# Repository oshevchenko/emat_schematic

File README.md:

# emat_schematic
Eagle schematic for 1000V power supply, HV switch, amplifier etc.

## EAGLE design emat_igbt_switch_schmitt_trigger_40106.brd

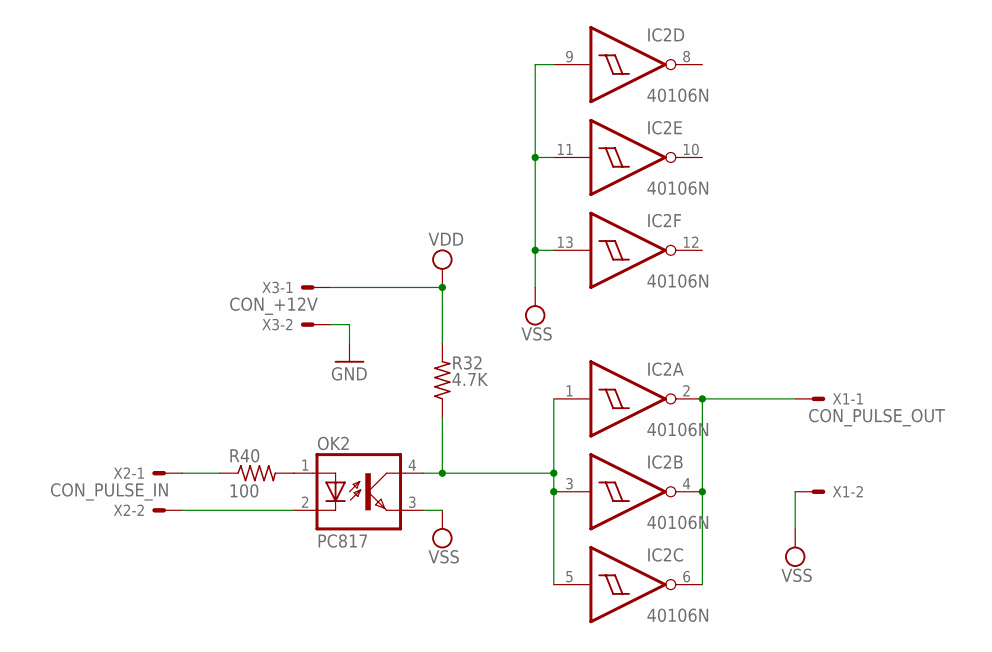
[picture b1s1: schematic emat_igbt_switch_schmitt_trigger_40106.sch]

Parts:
IC2: 40106N; DIL14
OK2: PC817; DIL04
R32: 4.7K; R1206
R40: 100; R1206
X1: CON_PULSE_OUT; 22-23-2021
X2: CON_PULSE_IN; 22-23-2021
X3: CON_+12V; 22-23-2021

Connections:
GND: X3.2
unnamed: IC2.2 (O), IC2.4 (O), IC2.6 (O), X1.1
unnamed: OK2.2 (C), X2.2
unnamed: IC2.1 (I), IC2.3 (I), IC2.5 (I), OK2.4 (COL), R32.1
unnamed: R40.1, X2.1
unnamed: OK2.1 (A), R40.2
VDD: IC2.14 (VDD), R32.2, X3.1
VSS: IC2.7 (VSS), IC2.9 (I), IC2.11 (I), IC2.13 (I), OK2.3 (EMIT), X1.2

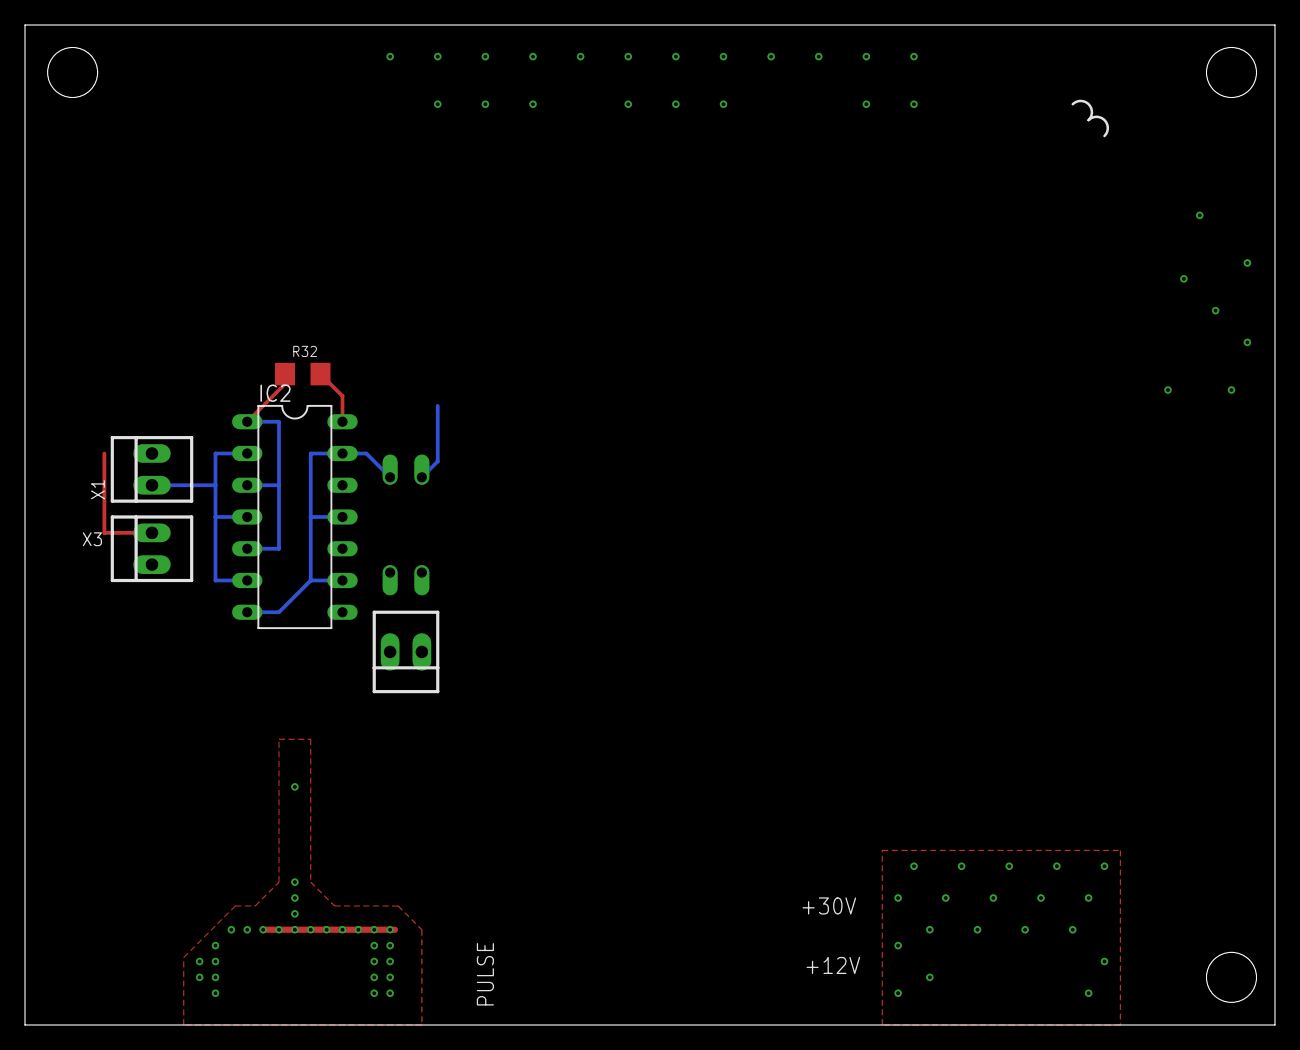
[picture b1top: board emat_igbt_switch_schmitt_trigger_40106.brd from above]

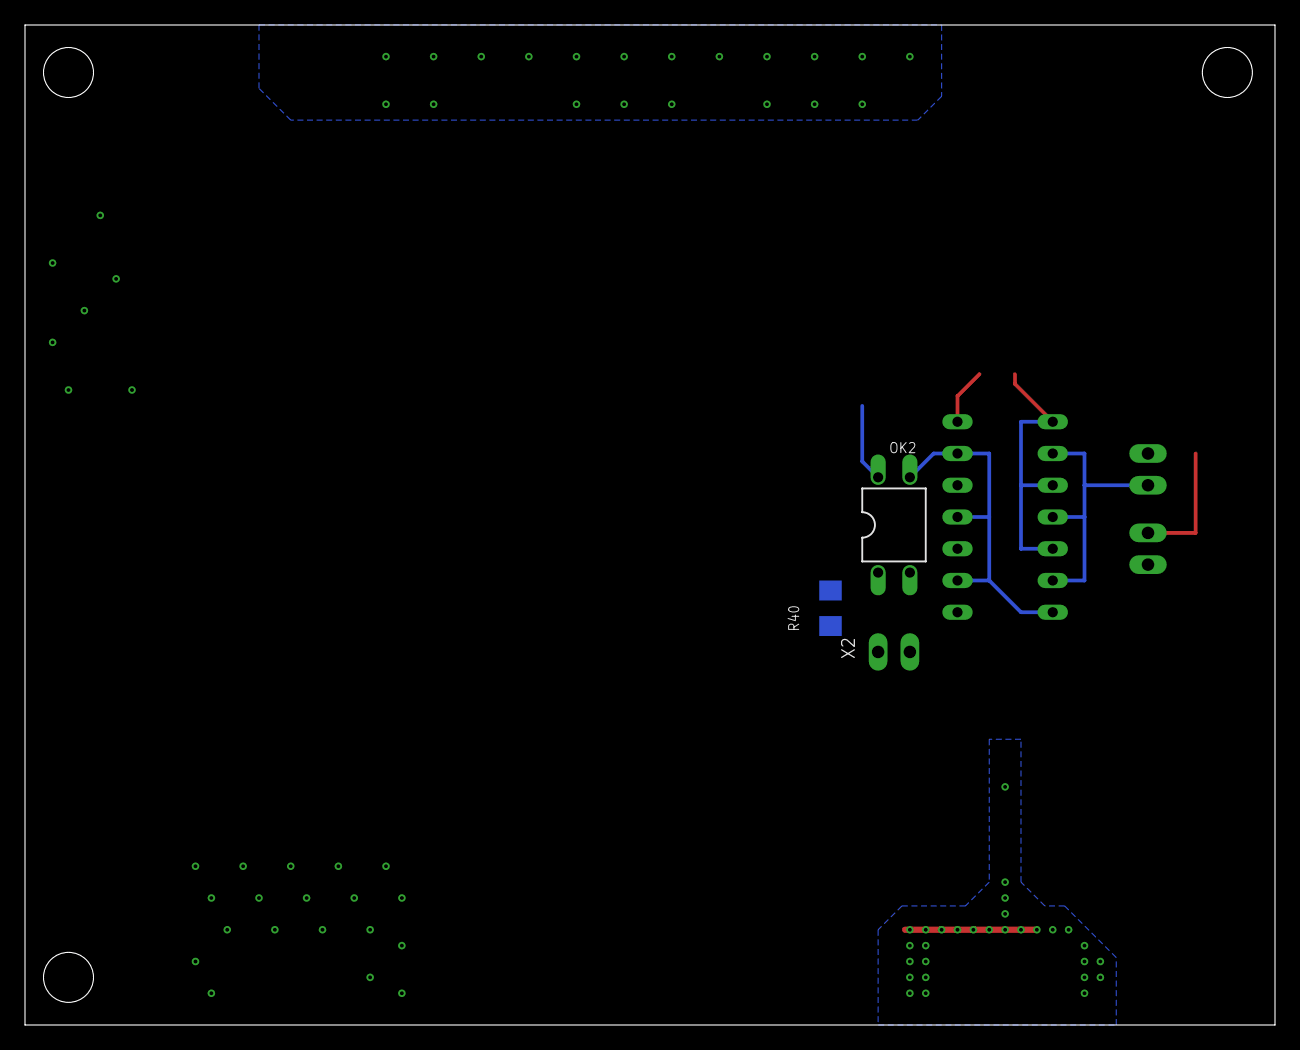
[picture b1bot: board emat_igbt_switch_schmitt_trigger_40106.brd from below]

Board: 2 copper layers, 100.0 x 80.0 mm, 7 parts (2 on the bottom side), 7 nets.

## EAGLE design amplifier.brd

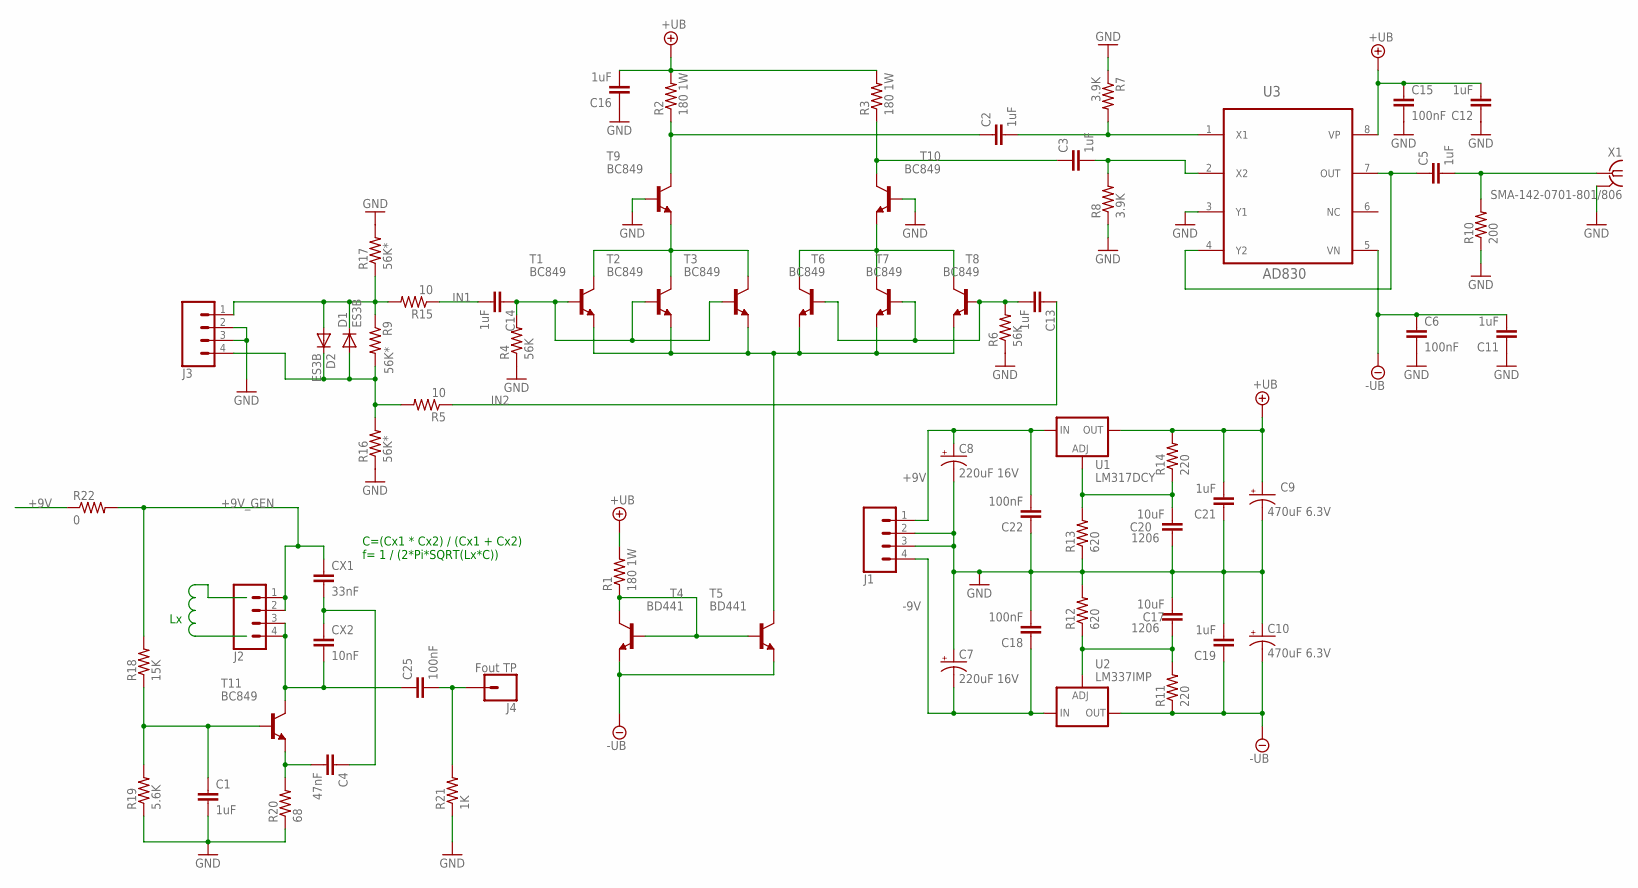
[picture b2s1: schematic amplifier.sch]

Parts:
C1, C2, C3, C5, C11, C12, C13, C14, C16, C19, C21: 1uF; C0805
C4: 47nF; C0805
C6, C15, C18, C22, C25: 100nF; C0805
C7, C8: 220uF 16V; 153CLV-1010
C9, C10: 470uF 6.3V; 153CLV-1010
C17, C20: 10uF; C1206
CX1: 33nF; C0805
CX2: 10nF; C0805
D1, D2: ES3B; SMC
J1, J2, J3: CONN_04LONGPADS; 1X04_LONGPADS
J4: Fout TP; SNAP-MALE
R1, R2, R3: 180 1W; R1206W
R4, R6: 56K; R1206W
R5, R15: 10; R1206W
R7, R8: 3.9K; R1206W
R9, R16, R17: 56K*; R1206W
R10: 200; R1206W
R11, R14: 220; R1206W
R12, R13: 620; R1206W
R18: 15K; R1206W
R19: 5.6K; R1206W
R20: 68; R1206W
R21: 1K; R1206W
R22: 0; R1206W
T1, T2, T3, T6, T7, T8, T9, T10, T11: BC849; SOT23
T4, T5: BD441; TO126
U1: LM317DCY; SOT223
U2: LM337IMP; SOT223
U3: AD830; SOIC127P600X175-8N
X1: SMA-142-0701-801/806; J502-ND-142-0701-801/806

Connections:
+9V: C8.+, C22.2, J1.1, R22.1, U1.3 (IN)
+9V_GEN: CX1.1, J2.1, J2.2, R18.2, R22.2
+UB: C9.+, C12.2, C15.1, C16.2, C21.2, R1.2, R2.2, R3.2, R14.2, U1.2 (OUT), U1.4 (OUT), U3.8 (VP)
-9V: C7.-, C18.1, J1.4, U2.2 (IN), U2.4 (IN)
-UB: C6.1, C10.-, C11.2, C19.1, R11.1, T4.1 (E), T5.1 (E), U2.3 (OUT), U3.5 (VN)
GND: C1.2, C6.2, C7.+, C8.-, C9.-, C10.+, C11.1, C12.1, C15.2, C16.1, C17.2, C18.2, C19.2, C20.1, C21.1, C22.1, J1.2, J1.3, J3.2, J3.3, R4.1, R6.1, R7.1, R8.1, R10.1, R12.2, R13.1, R16.1, R17.2, R19.1, R20.1, R21.1, T9.1 (B), T10.1 (B), U3.3 (Y1), X1.G@1 (2), X1.G@2 (2), X1.G@3 (2), X1.G@4 (2)
IN1: C14.2, R15.1
IN2: C13.1, R5.1
unnamed: D1.C, D2.A, J3.1, R9.1, R15.2, R17.1
unnamed: C17.1, R11.2, R12.1, U2.1 (ADJ)
unnamed: D1.A, D2.C, J3.4, R5.2, R9.2, R16.2
unnamed: R1.1, T4.2 (C), T4.3 (B), T5.3 (B)
unnamed: C25.1, CX2.2, J2.3, J2.4, T11.3 (C)
unnamed: C2.2, R7.2, U3.1 (X1)
unnamed: C25.2, J4.2, R21.2
unnamed: C20.2, R13.2, R14.1, U1.1 (ADJ)
unnamed: C4.1, CX1.2, CX2.1
unnamed: C4.2, R20.2, T11.2 (E)
unnamed: T1.2 (E), T2.2 (E), T3.2 (E), T5.2 (C), T6.2 (E), T7.2 (E), T8.2 (E)
unnamed: C1.1, R18.1, R19.2, T11.1 (B)
unnamed: C13.2, R6.2, T6.1 (B), T7.1 (B), T8.1 (B)
unnamed: C14.1, R4.2, T1.1 (B), T2.1 (B), T3.1 (B)
unnamed: T1.3 (C), T2.3 (C), T3.3 (C), T9.2 (E)
unnamed: T6.3 (C), T7.3 (C), T8.3 (C), T10.2 (E)
unnamed: C2.1, R2.1, T9.3 (C)
unnamed: C3.1, R3.1, T10.3 (C)
unnamed: C3.2, R8.2, U3.2 (X2)
unnamed: C5.1, U3.4 (Y2), U3.7 (OUT)
unnamed: C5.2, R10.2, X1.1
NC: U3.6 (NC)

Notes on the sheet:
C=(Cx1 * Cx2) / (Cx1 + Cx2) f= 1 / (2*Pi*SQRT(Lx*C))

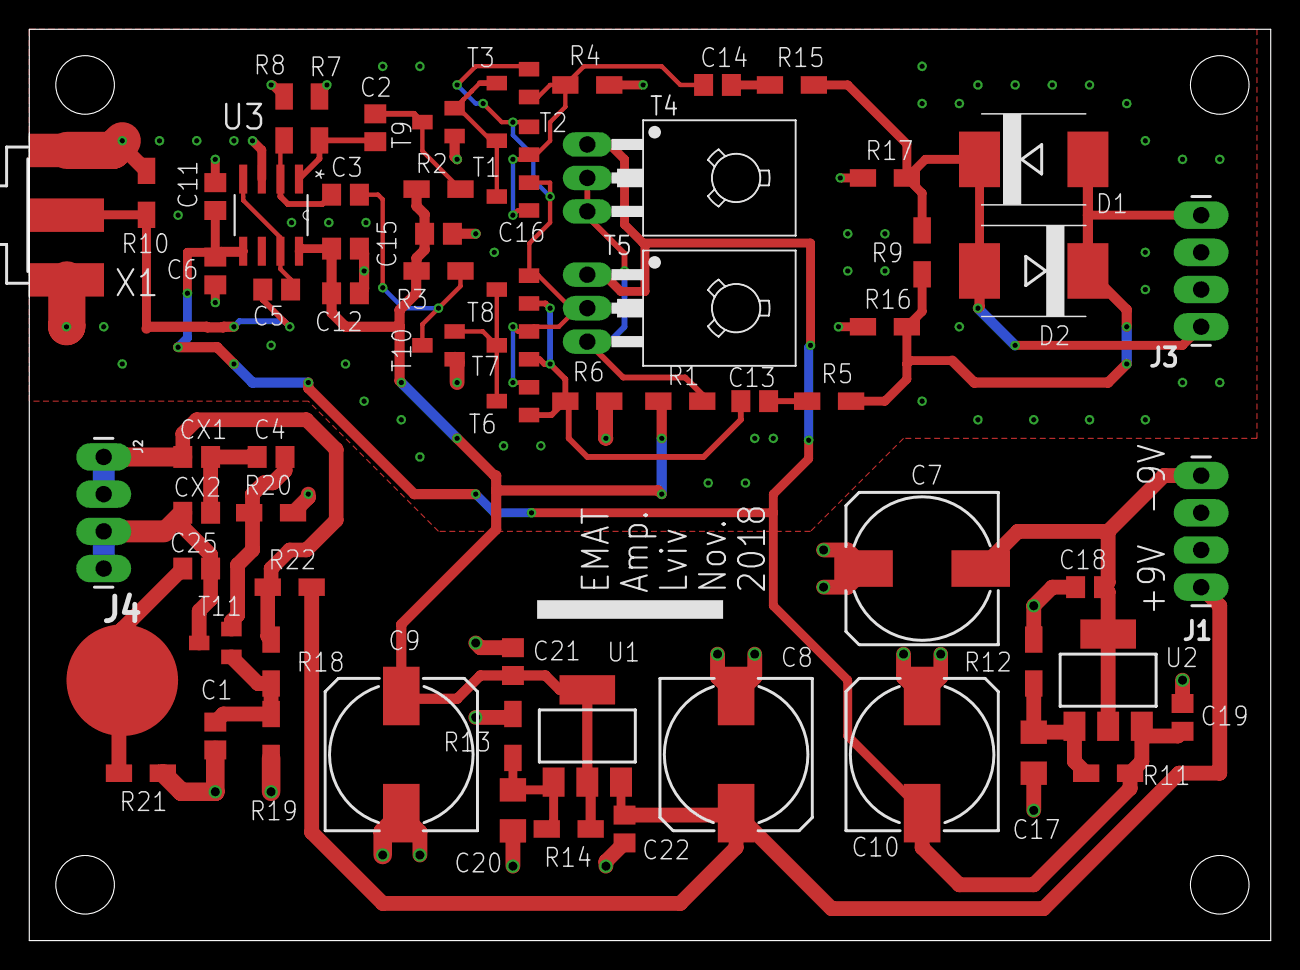
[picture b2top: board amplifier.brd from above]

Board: 2 copper layers, 84.8 x 62.2 mm, 68 parts (0 on the bottom side), 29 nets.

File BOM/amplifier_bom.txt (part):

Partlist exported from /home/oleksandr/EAGLE/projects/emat_schematic/amplifier.sch at 11/11/18 11:07 AM

Qty Value                Device               Package                  Parts                                             Description                                                                                                                              MF                 MPN          OC_FARNELL OC_NEWARK PACKAGE PROD_ID    SPICEPREFIX
3                        CONN_04LONGPADS      1X04_LONGPADS            J1, J2, J3                                        Multi connection point. Often used as Generic Header-pin footprint for 0.1 inch spaced/style header connections                                                                                       CONN-09696            
1   0                    R-US_R1206W          R1206W                   R22                                               RESISTOR, American symbol                                                                                                                                                                                                   
2   10                   R-US_R1206W          R1206W                   R5, R15                                           RESISTOR, American symbol                                                                                                                                                                                                   
5   100nF                C-EUC0805            C0805                    C6, C15, C18, C22, C25                            CAPACITOR, European symbol                                                                                                                                                                                                  
1   10nF                 C-EUC0805            C0805                    CX2                                               CAPACITOR, European symbol                                                                                                                                                                                                  
2   10uF                 C-EUC1206            C1206                    C17, C20                                          CAPACITOR, European symbol                                                                                                                                                                    1206                          
3   150 1W               R-US_R1206W          R1206W                   R1, R2, R3                                        RESISTOR, American symbol                                                                                                                                                                                                   
1   15K                  R-US_R1206W          R1206W                   R18                                               RESISTOR, American symbol                                                                                                                                                                                                   
1   1K                   R-US_R1206W          R1206W                   R21                                               RESISTOR, American symbol                                                                                                                                                                                                   
11  1uF                  C-EUC0805            C0805                    C1, C2, C3, C5, C11, C12, C13, C14, C16, C19, C21 CAPACITOR, European symbol                                                                                                                                                                                                  
1   200                  R-US_R1206W          R1206W                   R10                                               RESISTOR, American symbol                                                                                                                                                                                                   
2   220uF 16V            CPOL-US153CLV-1010   153CLV-1010              C7, C8                                            POLARIZED CAPACITOR, American symbol                                                                                                                                                                             C          
2   240                  R-US_R1206W          R1206W                   R11, R14                                          RESISTOR, American symbol                                                                                                                                                                                                   
2   3.9K                 R-US_R1206W          R1206W                   R7, R8                                            RESISTOR, American symbol                                                                                                                                                                                                   
1   33nF                 C-EUC0805            C0805                    CX1                                               CAPACITOR, European symbol                                                                                                                                                                                                  
2   470uF 6.3V           CPOL-US153CLV-1010   153CLV-1010              C9, C10                                           POLARIZED CAPACITOR, American symbol                                                                                                                                                                             C          
1   47nF                 C-EUC0805            C0805                    C4                                                CAPACITOR, European symbol                                                                                                                                                                                                  
1   5.6K                 R-US_R1206W          R1206W                   R19                                               RESISTOR, American symbol                                                                                                                                                                                                   
2   56K                  R-US_R1206W          R1206W                   R4, R6                                            RESISTOR, American symbol                                                                                                                                                                                                   
3   56K*                 R-US_R1206W          R1206W                   R9, R16, R17                                      RESISTOR, American symbol                                                                                                                                                                                                   
1   68                   R-US_R1206W          R1206W                   R20                                               RESISTOR, American symbol                                                                                                                                                                                                   
2   910                  R-US_R1206W          R1206W                   R12, R13                                          RESISTOR, American symbol                                                                                                                                                                                                   
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
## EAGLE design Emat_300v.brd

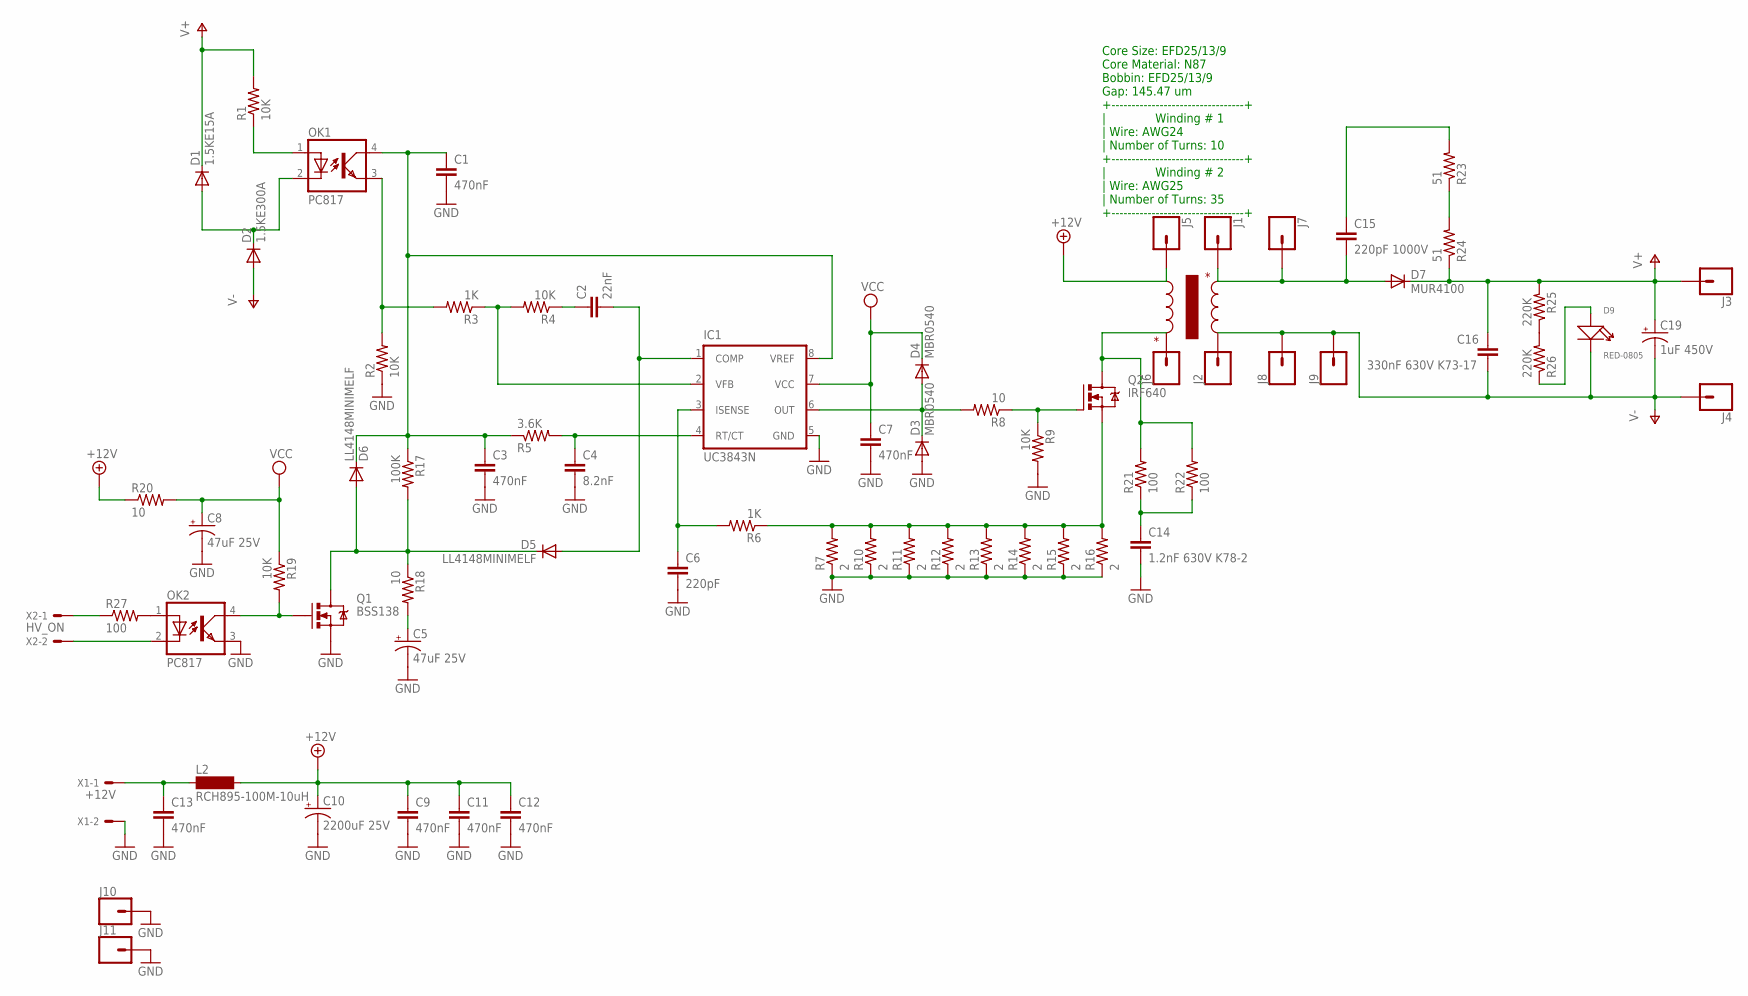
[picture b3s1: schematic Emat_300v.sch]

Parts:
C1, C3, C7, C9, C11, C12, C13: 470nF; C0805
C2: 22nF; C0805
C4: 8.2nF; C0805
C5, C8: 47uF 25V; E5-8,5
C6: 220pF; C0805
C10: 2200uF 25V; E7,5-18
C14: 1.2nF 630V K78-2; C150-064X183
C15: 220pF 1000V; C075-042X103
C16: 330nF 630V K73-17; C225-062X268
C19: 1uF 450V; E5-8,5
D1: 1.5KE15A; DO201-15
D2: 1.5KE300A; DO201-15
D3, D4: MBR0540; SOD123
D5, D6: LL4148MINIMELF; MINIMELF
D7: MUR4100; DO201-15
D9: RED-0805; LED-0805
IC1: UC3843N; DIL08
J1, J2, J3, J4, J5, J6, J7, J8, J9, J10, J11: CONN_01PTH_NO_SILK_KIT; 1X01NS_KIT
L2: RCH895-100M-10uH; BS11
OK1, OK2: PC817; DIL04
Q1: BSS138; SOT23-3
Q2: IRF640; TO220BV
R1, R2, R4, R9, R19: 10K; R1206
R3, R6: 1K; R1206
R5: 3.6K; R1206
R7, R10, R11, R12, R13, R14, R15, R16: 2; R1206
R8, R18, R20: 10; R1206
R17: 100K; R1206
R21, R22: 100; R2512
R23, R24: 51; R1206
R25, R26: 220K; R1206
R27: 100; R1206
X1: +12V; 22-23-2021
X2: HV_ON; 22-23-2021

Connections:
+12V: C9.1, C10.+, C11.1, C12.1, J5.1, L2.2, R20.1
GND: C1.2, C3.2, C4.2, C5.-, C6.2, C7.2, C8.-, C9.2, C10.-, C11.2, C12.2, C13.2, C14.2, D3.A, IC1.5 (GND), J10.1, J11.1, OK2.3 (EMIT), Q1.2 (S), R2.1, R7.1, R9.2, R10.1, R11.1, R12.1, R13.1, R14.1, R15.1, R16.1, X1.2
unnamed: D1.A, D2.C, OK1.2 (C)
unnamed: R25.1, R26.2
unnamed: OK1.1 (A), R1.1
unnamed: C5.+, R18.2
unnamed: OK1.3 (EMIT), R2.2, R3.2
unnamed: IC1.2 (VFB), R3.1, R4.2
unnamed: C2.1, R4.1
unnamed: C2.2, D5.A, IC1.1 (COMP)
unnamed: C4.1, IC1.4 (RT/CT), R5.2
unnamed: C6.1, IC1.3 (ISENSE), R6.2
unnamed: D3.C, D4.A, IC1.6 (OUT), R8.2
unnamed: Q2.G, R8.1, R9.1
unnamed: Q2.S, R6.1, R7.2, R10.2, R11.2, R12.2, R13.2, R14.2, R15.2, R16.2
unnamed: C1.1, C3.1, D6.C, IC1.8 (VREF), OK1.4 (COL), R5.1, R17.1
unnamed: D5.C, D6.A, Q1.3 (D), R17.2, R18.1
unnamed: C13.1, L2.1, X1.1
unnamed: OK2.4 (COL), Q1.1 (G), R19.2
unnamed: OK2.1 (A), R27.2
unnamed: OK2.2 (C), X2.2
unnamed: J6.1, Q2.D, R21.2, R22.2
unnamed: C14.1, R21.1, R22.1
unnamed: C15.2, D7.A, J1.1, J7.1
unnamed: R27.1, X2.1
unnamed: R23.1, R24.2
unnamed: C15.1, R23.2
unnamed: D9.+, R26.1
V+: C16.1, C19.+, D1.C, D7.C, J3.1, R1.2, R24.1, R25.2
V-: C16.2, C19.-, D2.A, D9.-, J2.1, J4.1, J8.1, J9.1
VCC: C7.1, C8.+, D4.C, IC1.7 (VCC), R19.1, R20.2

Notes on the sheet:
Core Size: EFD25/13/9 Core Material: N87 Bobbin: EFD25/13/9 Gap: 145.47 um +---------------------------------+ | Winding # 1 | Wire: AWG24 | Number of Turns: 10 +---------------------------------+ | Winding # 2 | Wire: AWG25 | Number of Turns: 35 +---------------------------------+

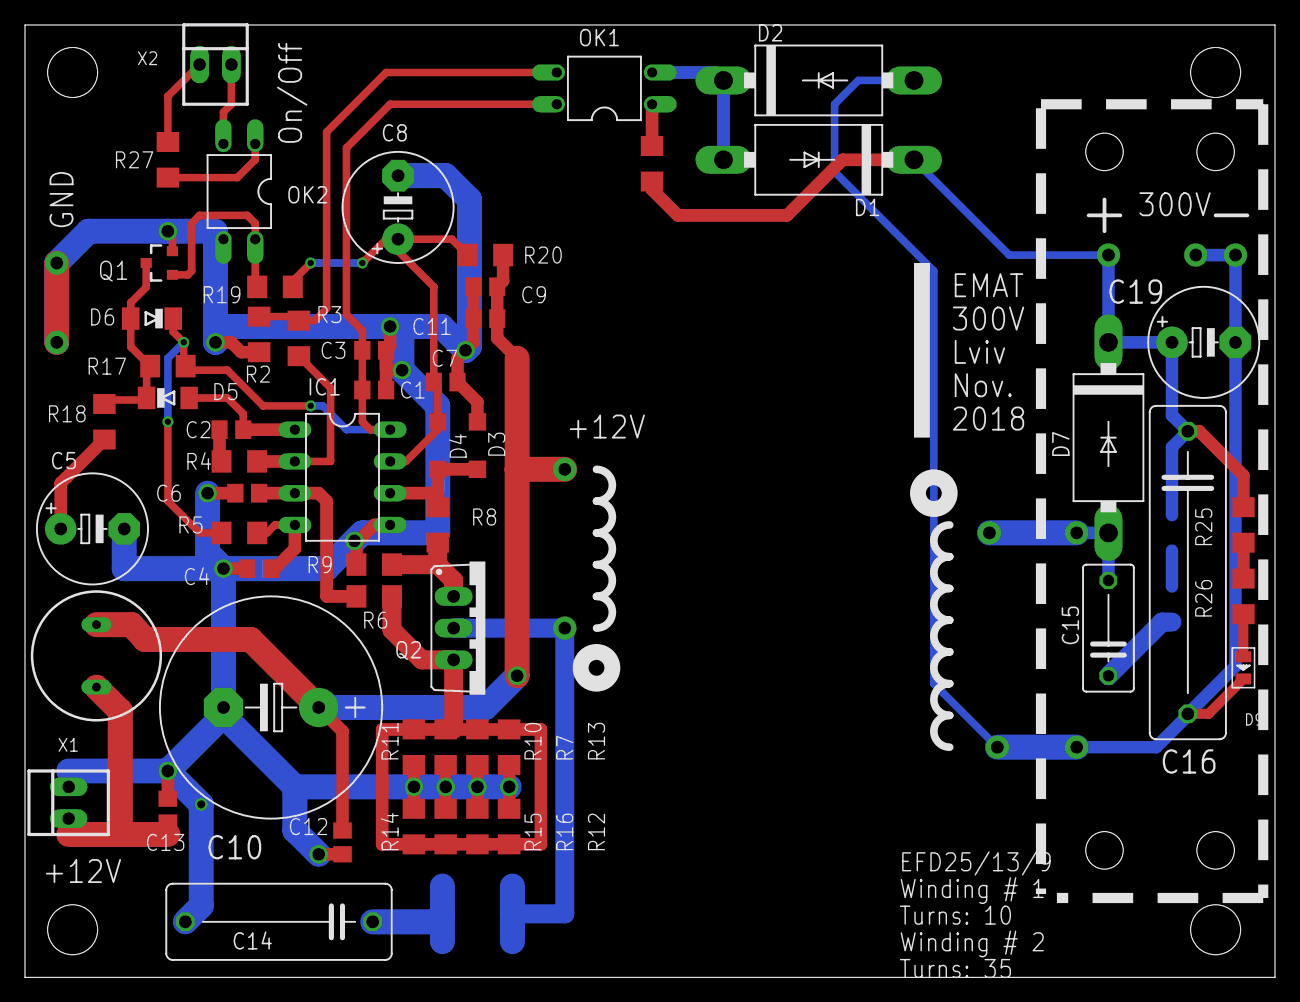
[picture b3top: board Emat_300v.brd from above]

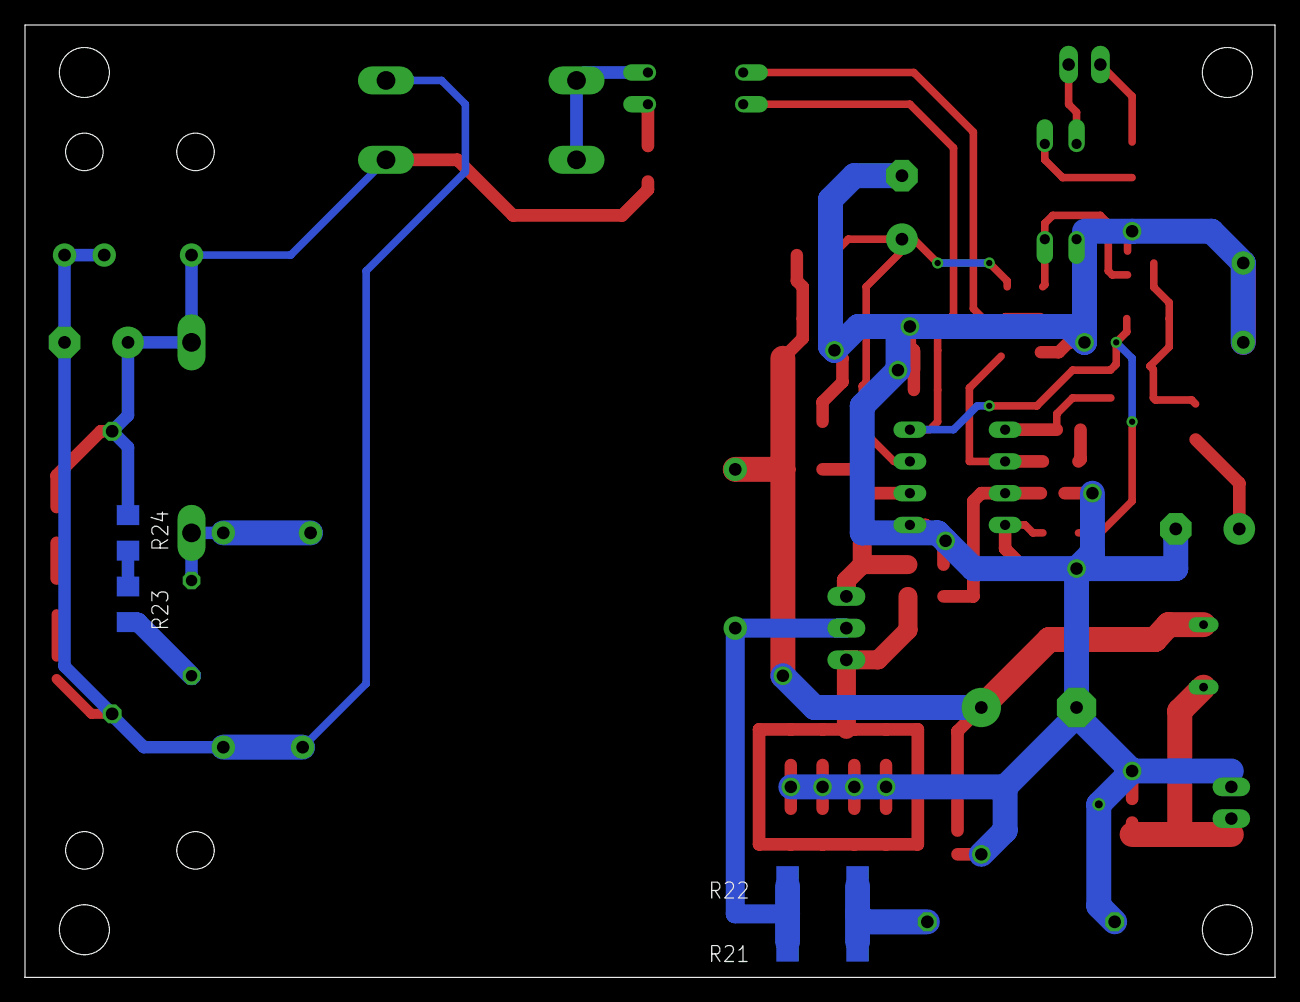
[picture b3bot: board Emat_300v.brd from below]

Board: 2 copper layers, 100.0 x 76.2 mm, 71 parts (4 on the bottom side), 31 nets.

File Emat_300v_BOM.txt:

Partlist exported from D:/workspace/EMAT/POC/Schematic/Emat/Emat_300v.sch at 4/7/2016 10:36 AM

Qty Value             Device                Package      Parts                                 Description
1   EFD25             EFD25                 EFD25        T1                                    TRANSFORMER
1   UC3843N           UC3843N               DIL08        IC1                                   SMPS Controller
1   BSS138            MOSFET-NCHANNELBSS138 SOT23-3      Q1                                    Common NMOSFET Parts
1   IRF640IW220B      IRF640IW220B          IW220B       Q2                                    HEXFET Power MOSFET
2   LL4148MINIMELF    LL4148MINIMELF        MINIMELF     D5, D6                                DIODE              
2   MBR0540           DIODE-SOD123          SOD123       D3, D4                                DIODE              
1   MUR4100           DIODE-DO201-15        DO201-15     D7                                    DIODE              
2   1.5KE15A          DIODE-DO201-15        DO201-15     D1, D2                                DIODE
2   PC817             PC817                 DIL04        OK1, OK2                              SHARP OPTO COUPLER
2   47uF 25V          CPOL-USE5-8.5         E5-8,5       C5, C8                                POLARIZED CAPACITOR
1   47uF 450V         CPOL-USE7.5-18        E7,5-18      C19                                   POLARIZED CAPACITOR
1   2200uF 25V        CPOL-USE7.5-18        E7,5-18      C10                                   POLARIZED CAPACITOR
1   1.2nF 630V K78-2  C-EU150-064X183       C150-064X183 C14                                   CAPACITOR
1   330nF 630V K73-17 C-EU225-062X268       C225-062X268 C16                                   CAPACITOR
1   220pF 1000V       C-EU075-042X103       C075-042X103 C15                                   CAPACITOR
1   220pF             C-EUC0805             C0805        C6                                    CAPACITOR
1   22nF              C-EUC0805             C0805        C2                                    CAPACITOR
7   470nF             C-EUC0805             C0805        C1, C3, C7, C9, C11, C12, C13         CAPACITOR
1   8.2nF             C-EUC0805             C0805        C4                                    CAPACITOR
2   100               R-US_R2512            R2512        R21, R22                              RESISTOR
3   10                R-US_R1206            R1206        R8, R18, R20                          RESISTOR
1   100K              R-US_R1206            R1206        R17                                   RESISTOR
5   10K               R-US_R1206            R1206        R1, R2, R4, R9, R19                   RESISTOR
2   1K                R-US_R1206            R1206        R3, R6                                RESISTOR
8   2                 R-US_R1206            R1206        R7, R10, R11, R12, R13, R14, R15, R16 RESISTOR
2   220K              R-US_R1206            R1206        R25, R26                              RESISTOR
1   3.6K              R-US_R1206            R1206        R5                                    RESISTOR
2   51                R-US_R1206            R1206        R23, R24                              RESISTOR
1   RCH895-100M-10uH  RCH-89511             BS11         L2                                    INDUCTOR
6   PIN1-2            PIN1-2                62221        J1, J2, J3, J4, J5, J6                CONN

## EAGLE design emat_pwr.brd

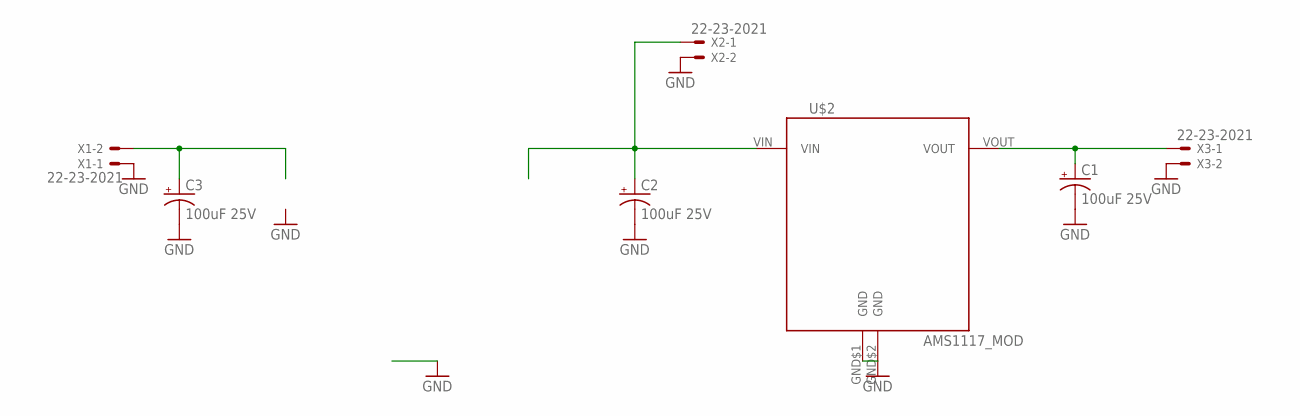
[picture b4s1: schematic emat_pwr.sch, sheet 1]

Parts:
C1, C2, C3: 100uF 25V; CPOL-RADIAL-100UF-25V
U$2: AMS1117_MOD
X1, X2, X3: 22-23-2021

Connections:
GND: C1.2 (-), C2.2 (-), C3.2 (-), U$2.GND$1 (GND), U$2.GND$2 (GND), X1.1, X2.2, X3.2; also elsewhere on the board
unnamed: C2.1 (+), U$2.VIN, X2.1
unnamed: C1.1 (+), U$2.VOUT, X3.1
unnamed: C3.1 (+), X1.2

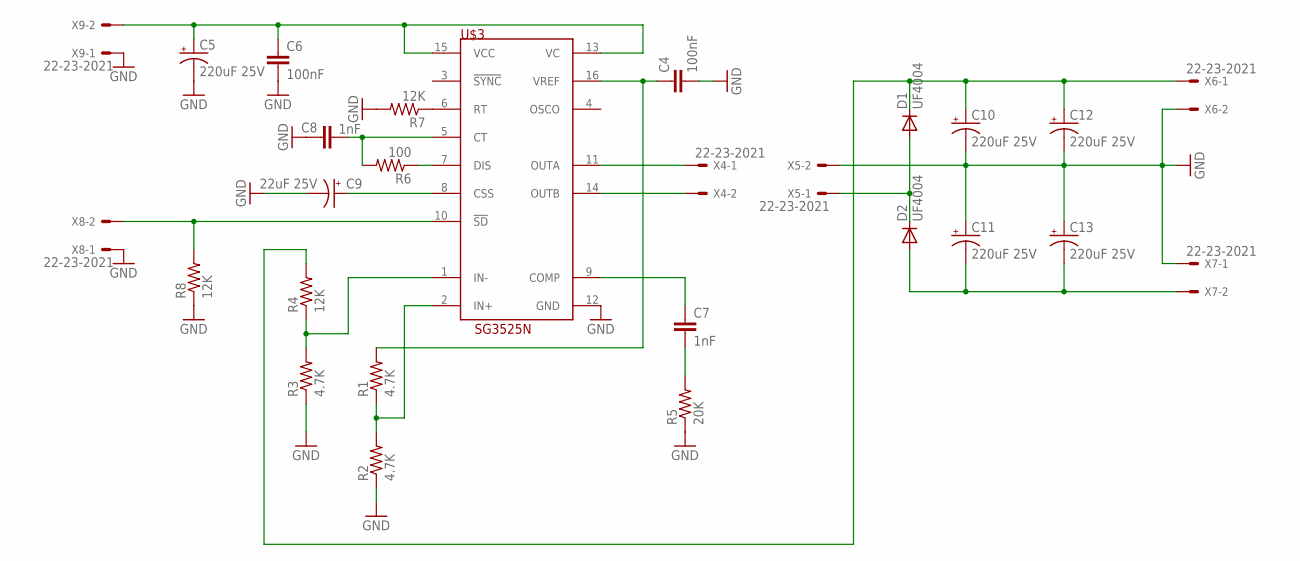
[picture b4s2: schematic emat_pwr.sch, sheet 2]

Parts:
C4, C6: 100nF; C0805
C5, C10, C11, C12, C13: 220uF 25V; E5-8,5
C7, C8: 1nF; C0805
C9: 22uF 25V; E5-8,5
D1, D2: UF4004; DO41-7.6
R1, R2, R3: 4.7K; R1206
R4, R7, R8: 12K; R1206
R5: 20K; R1206
R6: 100; R1206
U$3: SG3525N; DIL16
X4, X5, X6, X7, X8, X9: 22-23-2021

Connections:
COMP: C7.1, U$3.9 (COMP)
CSS: C9.+, U$3.8 (CSS)
GND: C4.2, C5.-, C6.2, C8.1, C9.-, C10.-, C11.+, C12.-, C13.+, R2.1, R3.1, R5.1, R7.2, R8.1, U$3.12 (GND), X5.2, X6.2, X7.1, X8.1, X9.1; also elsewhere on the board
IN-: R3.2, R4.1, U$3.1 (IN-)
unnamed: R1.1, R2.2, U$3.2 (IN+)
unnamed: C7.2, R5.2
unnamed: R6.1, U$3.7 (DIS)
unnamed: C8.2, R6.2, U$3.5 (CT)
unnamed: R7.1, U$3.6 (RT)
unnamed: D1.A, D2.C, X5.1
unnamed: C10.+, C12.+, D1.C, R4.2, X6.1
unnamed: C11.-, C13.-, D2.A, X7.2
unnamed: R8.2, U$3.10 (!SD), X8.2
OUTA: U$3.11 (OUTA), X4.1
OUTB: U$3.14 (OUTB), X4.2
VCC: C5.+, C6.1, U$3.13 (VC), U$3.15 (VCC), X9.2
VREF: C4.1, R1.2, U$3.16 (VREF)

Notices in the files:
parts and their libraries:
SparkFun-DiscreteSemi: Licensing: Creative Commons ShareAlike 4.0 International - https://creativecommons.org/licenses/by-sa/4.0
